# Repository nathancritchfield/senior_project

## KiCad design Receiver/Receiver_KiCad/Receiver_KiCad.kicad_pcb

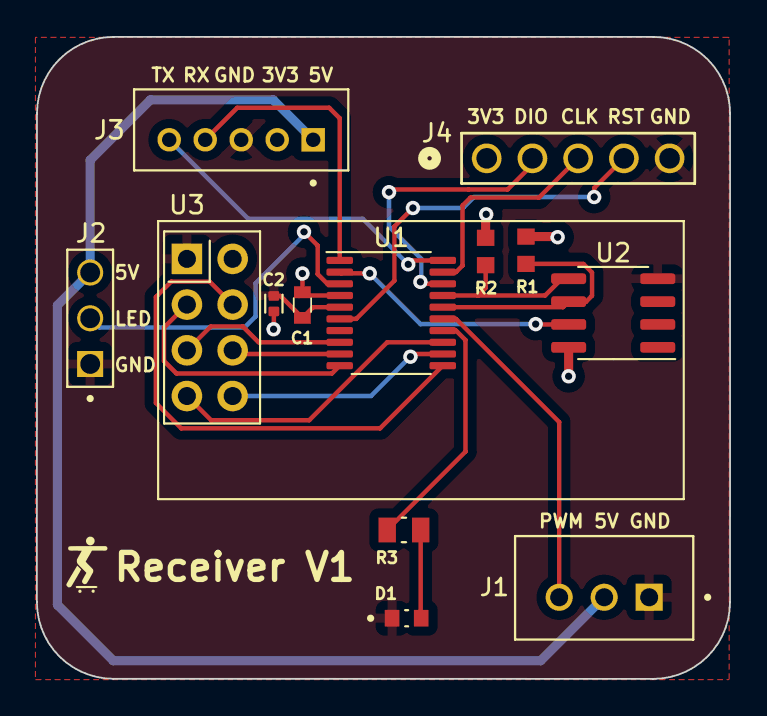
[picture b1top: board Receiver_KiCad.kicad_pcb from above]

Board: 2 copper layers, 38.5 x 35.7 mm, 13 parts (0 on the bottom side), 21 nets.

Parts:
C1: 4u7; CAPC1608X90N
C2: 100n; CAPC1005X55N
D1: LTST-C190GKT; LEDC1608X35N
J1: B3B-XH-A; JST_B3B-XH-A
J2: 61300311121; WURTH_61300311121
J3: B5B-PH-K-S; JST_B5B-PH-K-S
J4: 61300511121; CONN5_0511121_WRE
R1, R2: 4.7k; RESC1508X55N
R3: 120; RESC2012X65N
U1: STM32G031F8Px; TSSOP-20_4.4x6.5mm_P0.65mm
U2: FM24CL16B; SOIC-8_3.9x4.9mm_P1.27mm
U3: NRF24L01_Breakout; nRF24L01_Breakout

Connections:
+5V: J1.2, J2.03, J3.1
/MCU/I2C_SCL: R1.2, U1.16 (PA11/PA9), U2.6 (SCL)
/MCU/I2C_SDA: R2.2, U1.17 (PA12/PA10), U2.5 (SDA)
/MCU/PWM_OUT: J1.3, U1.15 (PB0/PB1/PB2/PA8)
/MCU/SK6812_OUT: J2.02, U1.3 (PC15)
/MCU/SPI1_CE: U1.10 (PA3), U3.3 (CE)
/MCU/SPI1_CSN: U1.11 (PA4), U3.4 (~CSN)
/MCU/SPI1_IRQ: U1.12 (PA5), U3.8 (IRQ)
/MCU/SPI1_MISO: U1.13 (PA6), U3.7 (MISO)
/MCU/SPI1_MOSI: U1.9 (PA2), U3.6 (MOSI)
/MCU/SPI1_SCK: U1.8 (PA1), U3.5 (SCK)
/MCU/STATUS_LED: R3.1, U1.14 (PA7)
/MCU/UART1_RX: J3.4, U1.1 (PB7/PB8)
/MCU/UART1_TX: J3.5, U1.20 (PB3/PB4/PB5/PB6)
/MCU/WP: U1.2 (PC14/PB9), U2.7 (WP)
GND: C1.2, C2.2, D1.C, J1.1, J2.01, J3.3, J4.5, U1.5 (VSS), U2.4 (VSS), U3.1 (GND)
unnamed: D1.A, R3.2
unnamed: J4.2, U1.18 (PA13)
unnamed: J4.3, U1.19 (PA14/PA15)
unnamed: J4.4, U1.6 (PF2)
VDD: C1.1, C2.1, J3.2, J4.1, R1.1, R2.1, U1.4 (VDD), U2.8 (VDD), U3.2 (VCC)

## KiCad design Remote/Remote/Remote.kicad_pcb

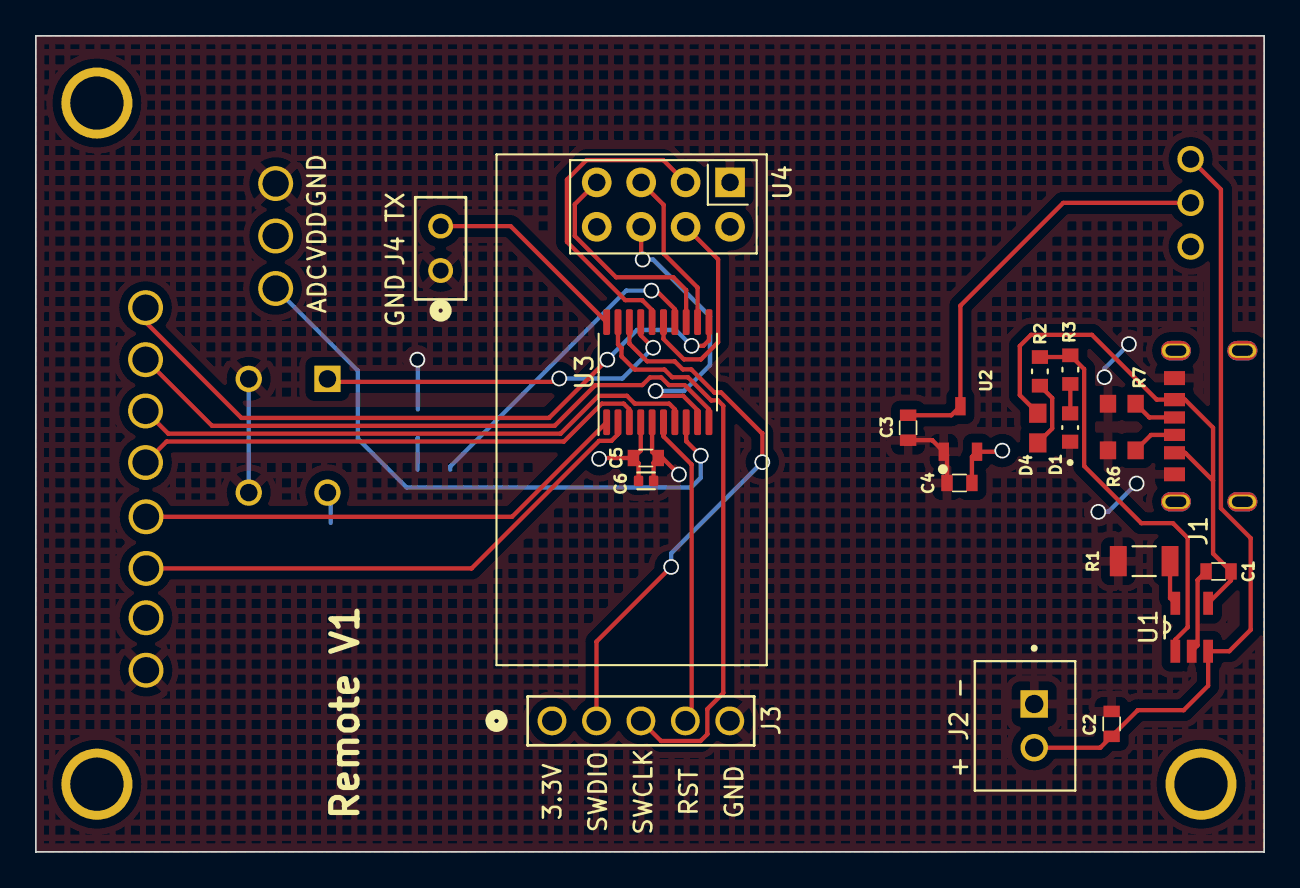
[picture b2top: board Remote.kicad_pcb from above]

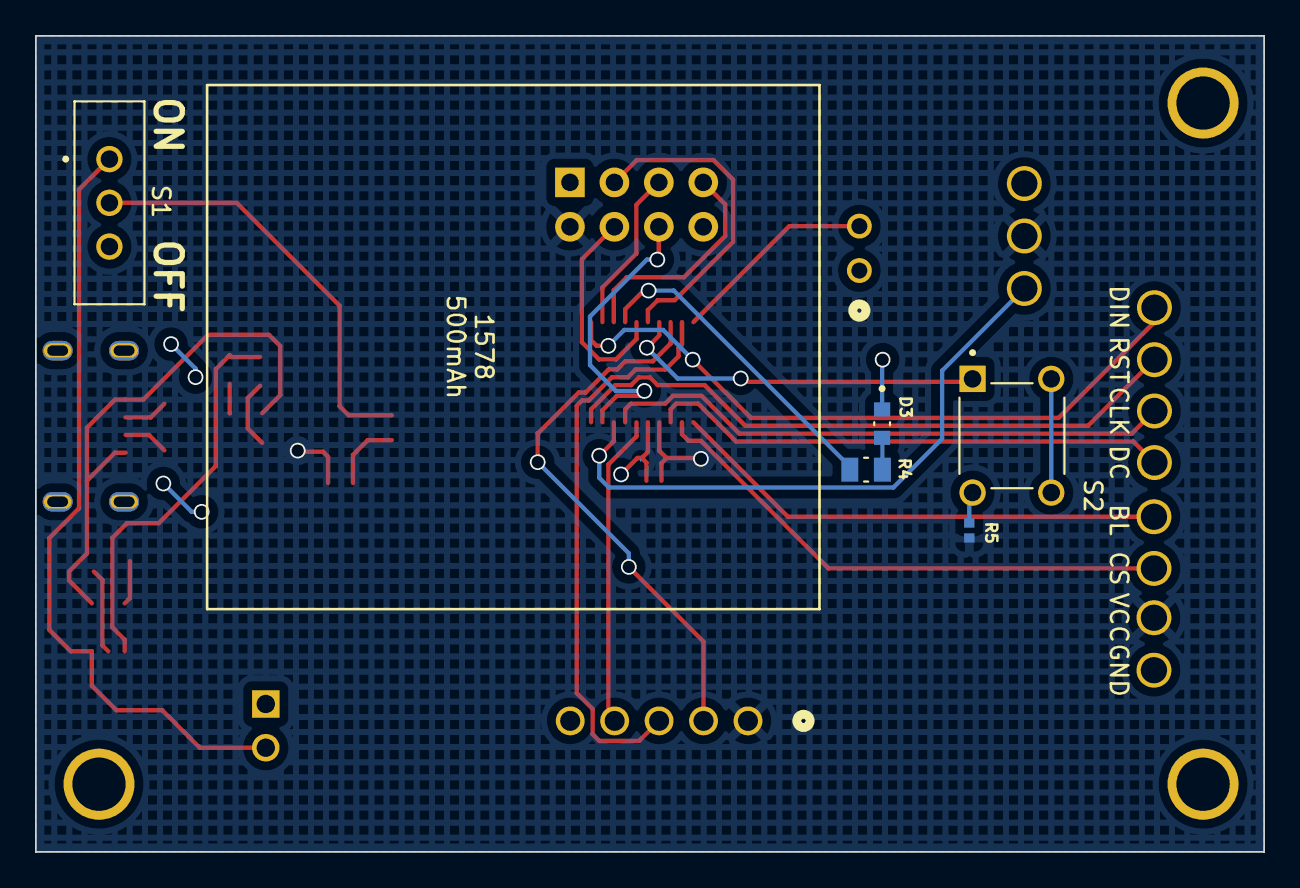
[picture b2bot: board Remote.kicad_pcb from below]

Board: 2 copper layers, 70.2 x 46.7 mm, 37 parts (13 on the bottom side), 31 nets.

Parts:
C1, C2, C3, C4, C5: 4u7; CAPC1608X90N
C6: 100n; CAPC1005X55N
D1: Ready; LEDC1608X35N
D3: LTST-C190GKT; LEDC1608X35N
D4: Charging; 0603
J1: USB4125-GF-A_REVA2; GCT_USB4125-GF-A_REVA2
J2: B2B-XH-A; JST_B2B-XH-A
J3: 61300511121; CONN5_0511121_WRE
J4: M20-9990246; CONN2_M20-999_1x2_HRW
R1: 5k; RESC3116X65N
R2, R3: 250; RESC1608X55N
R4: 120; RESC2012X65N
R5: 4.7k; RESC1005X40N
R6, R7: 5.1k; RESC1608X50N
S1: EG1218; SW_EG1218
S2: TL1105BF160Q; SW_TL1105BF160Q
U1: MCP73831T-2DCI_OT; SOT95P270X145-5N
U2: AP2210N-3.3TRG1; SOT95P280X145-3N
U3: STM32G030F6Px; TSSOP-20_4.4x6.5mm_P0.65mm
U4: NRF24L01_Breakout; nRF24L01_Breakout
U5: ADC; Wire_Via
U6: VDD; Wire_Via
U7, U9: GND; Wire_Via
U8: VCC; Wire_Via
U10: DIN; Wire_Via
U11: CLK; Wire_Via
U12: CS; Wire_Via
U13: DC; Wire_Via
U14: RST; Wire_Via
U15: BL; Wire_Via

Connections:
+5V: C1.1, D4.2, J1.A9 (VBUS), J1.B9 (VBUS__1), U1.4 (VDD)
+BATT: C2.2, J2.2, S1.1, U1.3 (VBAT)
/MCU/ADC1_IN1: U3.8 (PA1), U5.1
/MCU/Button: S2.1, U3.17 (PA12/PA10)
/MCU/Display_BL: U3.1 (PB7/PB8), U15.1
/MCU/Display_DC: U3.3 (PC15), U13.1
/MCU/Display_RST: U3.10 (PA3), U14.1
/MCU/GPIO_Output: R4.1, U3.14 (PA7)
/MCU/SPI1_CE: U3.16 (PA11/PA9), U4.3 (CE)
/MCU/SPI1_CSN: U3.15 (PB0/PB1/PB2/PA8), U4.4 (~CSN)
/MCU/SPI1_MISO: U3.13 (PA6), U4.7 (MISO)
/MCU/SPI1_MOSI: U3.9 (PA2), U4.6 (MOSI)
/MCU/SPI1_SCK: U3.12 (PA5), U4.5 (SCK)
/MCU/SPI2_CS: U3.2 (PC14/PB9), U12.1
/MCU/SPI2_MOSI: U3.11 (PA4), U10.1
/MCU/SPI2_SCK: U3.7 (PA0), U11.1
/MCU/USART1_TX: J4.2, U3.20 (PB3/PB4/PB5/PB6)
GND: C1.2, C2.1, C3.2, C4.1, C5.2, C6.2, D1.C, D3.C, J1.A12 (GND), J1.B12 (GND__1), J2.1, J3.5, J4.1, R1.1, R6.1, R7.1, S2.3, S2.4, U1.2 (VSS), U2.1 (GND), U3.5 (VSS), U4.1 (GND), U7.1, U9.1
unnamed: D1.A, R3.1
unnamed: D3.A, R4.2
unnamed: D4.1, R2.1
unnamed: J1.A5 (CC1), R6.2
unnamed: J1.B5 (CC2), R7.2
unnamed: R5.1, S2.2
unnamed: R1.2, U1.5 (PROG)
unnamed: R2.2, R3.2, U1.1 (STAT)
unnamed: C3.1, S1.2, U2.3 (VIN)
unnamed: J3.4, U3.6 (NRST)
unnamed: J3.2, U3.18 (PA13)
unnamed: J3.3, U3.19 (PA14/PA15)
VDD: C4.2, C5.1, C6.1, J3.1, R5.2, U2.2 (VOUT), U3.4 (VDD), U4.2 (VCC), U6.1, U8.1

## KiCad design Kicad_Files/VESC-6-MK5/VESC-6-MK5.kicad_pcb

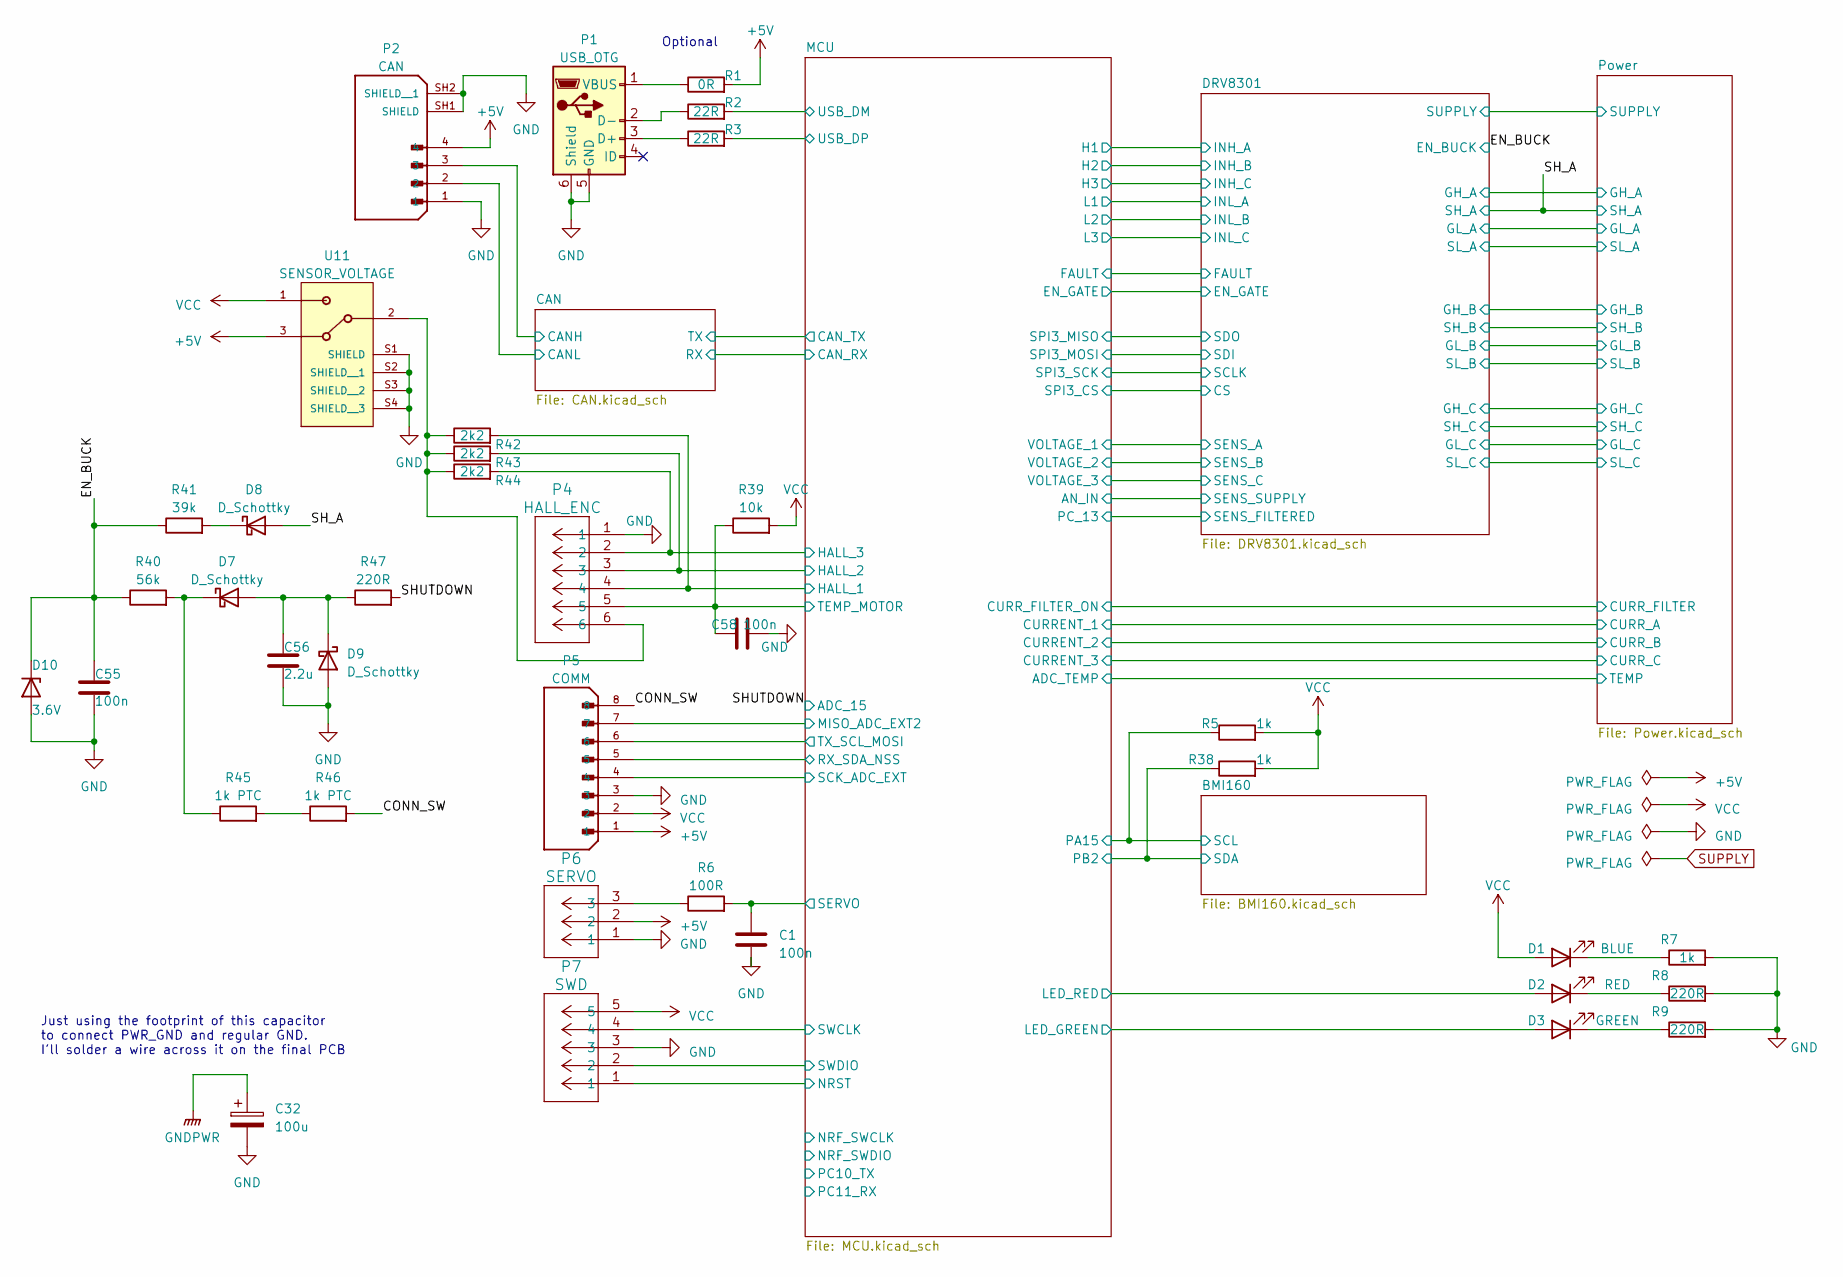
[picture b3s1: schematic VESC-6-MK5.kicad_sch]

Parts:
C1: 100n; CAPC2012X88N
C32: 100u; CAP_TPS1210_3P5X2P8_AVX
C55, C58: 100n; 0603_AVX
C56: 2.2u; CAPC1608X90N
D1: BLUE; LED_LTST-C191KRKT_LTO
D2: RED; LED_LTST-C191KRKT_LTO
D3: GREEN; LED_LTST-C191KGKT_LTO
D7, D8, D9: D_Schottky; CFP3_SOD123W_NEX
D10: 3.6V; SOD-882_TOS
P1: USB_OTG; CONN_S6B-PH-SM4-TBLFSN_JST
P2: CAN; JST_B4B-PH-SM4-TB__LF__SN_; PARTREV N/A
P4: HALL_ENC; CONN_S6B-PH-SM4-TBLFSN_JST
P5: COMM; JST_B8B-PH-SM4-TB_LF__SN_; PARTREV N/A
P6: SERVO; CONN_B3B-PH-SM4-TB_JST
P7: SWD; CONN5_4-TBLFSN_JST
R1: 0R; RESC1608X55N
R2, R3: 22R; RESC3216X70N
R5, R7, R38: 1k; RESC3216X70N
R6: 100R; RES_RK73H2A_KOA
R8, R9, R47: 220R; RESC3216X75N
R39: 10k; RESC1608X55N
R40: 56k; RESC1608X55N
R41: 39k; RESC1608X55N
R42, R43, R44: 2k2; RESC2012X60N
R45, R46: 1k PTC; RESC1608X55N
U11: SENSOR_VOLTAGE; SW_PCM12SMTR; DigiKey_Part_Number 401-2016-2-ND

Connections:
/BMI160/SCL: R5.1; also elsewhere on the board
/BMI160/SDA: R38.1; also elsewhere on the board
/CAN/CANH: P2.3; also elsewhere on the board
/CAN/CANL: P2.2; also elsewhere on the board
/CONN_SW: P5.8, R46.2
/EN_BUCK: C55.1, D10.1 (K), R40.1, R41.1; also elsewhere on the board
/MCU/HALL_1: P4.4, R42.2; also elsewhere on the board
/MCU/HALL_2: P4.3, R43.2; also elsewhere on the board
/MCU/HALL_3: P4.2, R44.2; also elsewhere on the board
/MCU/LED_GREEN: D3.2 (A); also elsewhere on the board
/MCU/LED_RED: D2.2 (A); also elsewhere on the board
/MCU/MISO_ADC_EXT2: P5.7; also elsewhere on the board
/MCU/NRST: P7.1; also elsewhere on the board
/MCU/RX_SDA_NSS: P5.5; also elsewhere on the board
/MCU/SCK_ADC_EXT: P5.4; also elsewhere on the board
/MCU/SERVO: C1.1, R6.2; also elsewhere on the board
/MCU/SWCLK: P7.4; also elsewhere on the board
/MCU/SWDIO: P7.2; also elsewhere on the board
/MCU/TEMP_MOTOR: C58.1, P4.5, R39.1; also elsewhere on the board
/MCU/TX_SCL_MOSI: P5.6; also elsewhere on the board
/MCU/USB_DM: R2.2; also elsewhere on the board
/MCU/USB_DP: R3.2; also elsewhere on the board
/SHUTDOWN: R47.2; also elsewhere on the board
/SH_A: D8.2 (A); also elsewhere on the board
GND: C1.2, C32.2, C55.2, C56.2, C58.2, D9.2 (A), D10.2 (A), P1.5 (GND), P1.6 (Shield), P2.1, P2.SH1 (SHIELD), P2.SH2 (SHIELD__1), P4.1, P5.3, P6.1, P7.3, R7.2, R8.2, R9.2, U11.S1 (SHIELD), U11.S2 (SHIELD__1), U11.S3 (SHIELD__2), U11.S4 (SHIELD__3); also elsewhere on the board
unnamed: D1.1 (K), R7.1
unnamed: D2.1 (K), R8.1
unnamed: D3.1 (K), R9.1
unnamed: C56.1, D7.2 (A), D9.1 (K), R47.1
unnamed: D7.1 (K), R40.2, R45.1
unnamed: D8.1 (K), R41.2
unnamed: P1.3 (D+), R3.1
unnamed: P1.2 (D-), R2.1
unnamed: P1.1 (VBUS), R1.1
unnamed: P4.6, R42.1, R43.1, R44.1, U11.2
unnamed: P6.3, R6.1
unnamed: R45.2, R46.1
VCC: D1.2 (A), P5.2, P7.5, R5.2, R38.2, R39.2, U11.1; also elsewhere on the board

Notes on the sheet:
Just using the footprint of this capacitor to connect PWR_GND and regular GND. I'll solder a wire across it on the final PCB
Optional

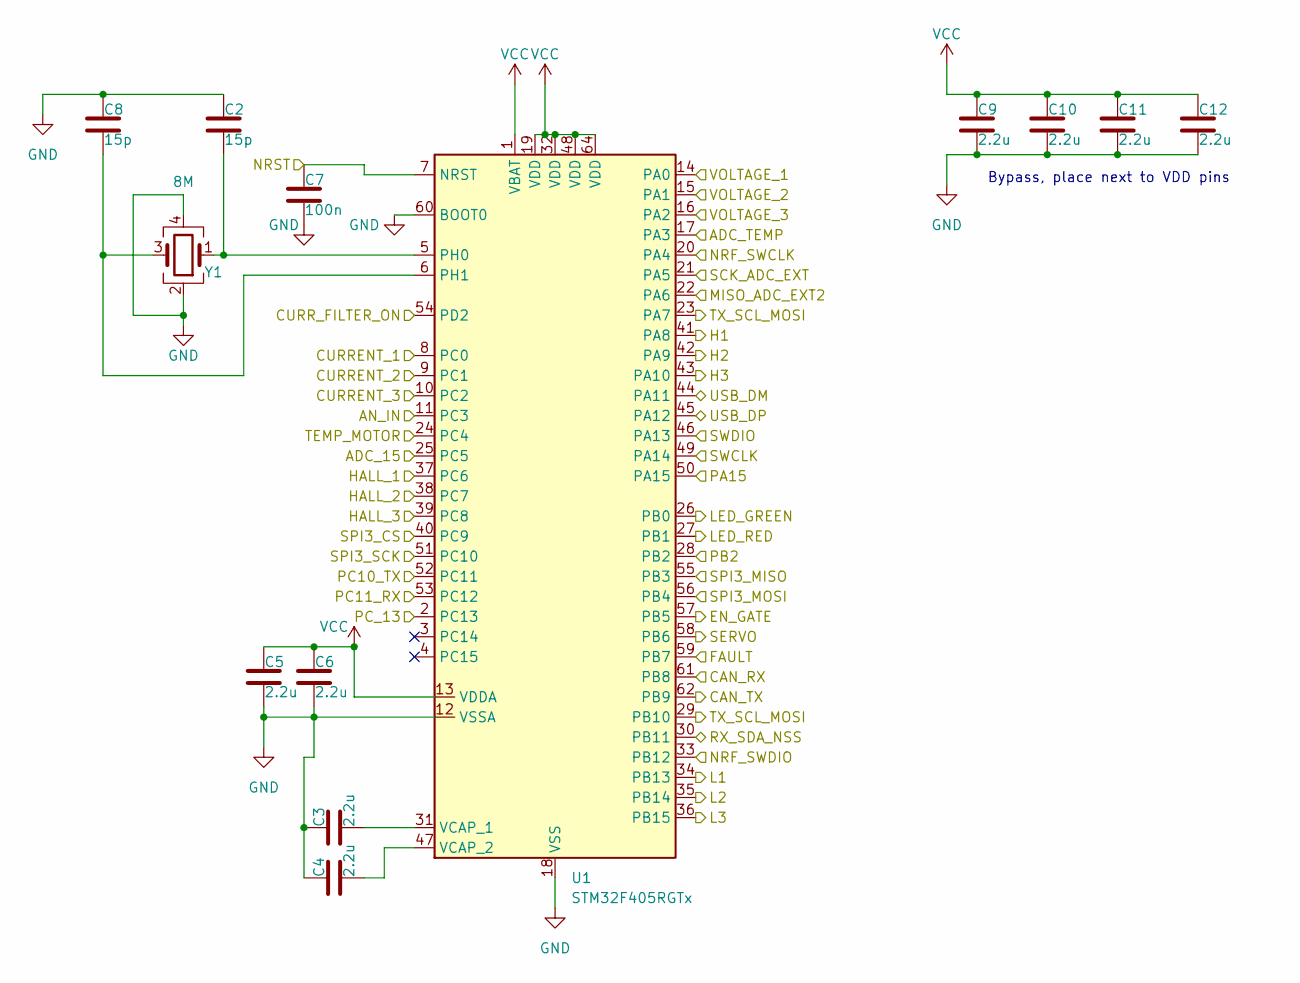
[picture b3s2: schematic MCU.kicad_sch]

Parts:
C2, C8: 15p; CAP_0402C_AVX
C3, C4, C5, C6, C9, C10, C11, C12: 2.2u; CAPC1608X90N
C7: 100n; 0603_AVX
U1: STM32F405RGTx; LQFP-64_10x10mm_P0.5mm
Y1: 8M; XTAL_ABM3B-8.000MHZ-10-1-U-T

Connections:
/BMI160/SCL: U1.50 (PA15); also elsewhere on the board
/BMI160/SDA: U1.28 (PB2); also elsewhere on the board
/CAN/RX: U1.61 (PB8); also elsewhere on the board
/CAN/TX: U1.62 (PB9); also elsewhere on the board
/DRV8301/CS: U1.40 (PC9); also elsewhere on the board
/DRV8301/EN_GATE: U1.57 (PB5); also elsewhere on the board
/DRV8301/FAULT: U1.59 (PB7); also elsewhere on the board
/DRV8301/INH_A: U1.41 (PA8); also elsewhere on the board
/DRV8301/INH_B: U1.42 (PA9); also elsewhere on the board
/DRV8301/INH_C: U1.43 (PA10); also elsewhere on the board
/DRV8301/INL_A: U1.34 (PB13); also elsewhere on the board
/DRV8301/INL_B: U1.35 (PB14); also elsewhere on the board
/DRV8301/INL_C: U1.36 (PB15); also elsewhere on the board
/DRV8301/SCLK: U1.51 (PC10); also elsewhere on the board
/DRV8301/SDI: U1.56 (PB4); also elsewhere on the board
/DRV8301/SDO: U1.55 (PB3); also elsewhere on the board
/DRV8301/SENS_A: U1.14 (PA0); also elsewhere on the board
/DRV8301/SENS_B: U1.15 (PA1); also elsewhere on the board
/DRV8301/SENS_C: U1.16 (PA2); also elsewhere on the board
/DRV8301/SENS_FILTERED: U1.2 (PC13); also elsewhere on the board
/DRV8301/SENS_SUPPLY: U1.11 (PC3); also elsewhere on the board
/MCU/ADC_TEMP: U1.17 (PA3); also elsewhere on the board
/MCU/CURRENT_1: U1.8 (PC0); also elsewhere on the board
/MCU/CURRENT_2: U1.9 (PC1); also elsewhere on the board
/MCU/CURRENT_3: U1.10 (PC2); also elsewhere on the board
/MCU/CURR_FILTER_ON: U1.54 (PD2); also elsewhere on the board
/MCU/HALL_1: U1.37 (PC6); also elsewhere on the board
/MCU/HALL_2: U1.38 (PC7); also elsewhere on the board
/MCU/HALL_3: U1.39 (PC8); also elsewhere on the board
/MCU/LED_GREEN: U1.26 (PB0); also elsewhere on the board
/MCU/LED_RED: U1.27 (PB1); also elsewhere on the board
/MCU/MISO_ADC_EXT2: U1.22 (PA6); also elsewhere on the board
/MCU/NRF_SWCLK: U1.20 (PA4)
/MCU/NRF_SWDIO: U1.33 (PB12)
/MCU/NRST: C7.1, U1.7 (NRST); also elsewhere on the board
/MCU/PC10_TX: U1.52 (PC11)
/MCU/PC11_RX: U1.53 (PC12)
/MCU/RX_SDA_NSS: U1.30 (PB11); also elsewhere on the board
/MCU/SCK_ADC_EXT: U1.21 (PA5); also elsewhere on the board
/MCU/SERVO: U1.58 (PB6); also elsewhere on the board
/MCU/SWCLK: U1.49 (PA14); also elsewhere on the board
/MCU/SWDIO: U1.46 (PA13); also elsewhere on the board
/MCU/TEMP_MOTOR: U1.24 (PC4); also elsewhere on the board
/MCU/TX_SCL_MOSI: U1.23 (PA7), U1.29 (PB10); also elsewhere on the board
/MCU/USB_DM: U1.44 (PA11); also elsewhere on the board
/MCU/USB_DP: U1.45 (PA12); also elsewhere on the board
/SHUTDOWN: U1.25 (PC5); also elsewhere on the board
GND: C2.1, C3.1, C4.1, C5.2, C6.2, C7.2, C8.1, C9.2, C10.2, C11.2, C12.2, U1.12 (VSSA), U1.18 (VSS), U1.60 (BOOT0), U1.63 (VSS), Y1.2, Y1.4; also elsewhere on the board
unnamed: C2.2, U1.5 (PH0), Y1.1
unnamed: C8.2, U1.6 (PH1), Y1.3
unnamed: C3.2, U1.31 (VCAP_1)
unnamed: C4.2, U1.47 (VCAP_2)
VCC: C5.1, C6.1, C9.1, C10.1, C11.1, C12.1, U1.1 (VBAT), U1.13 (VDDA), U1.19 (VDD), U1.32 (VDD), U1.48 (VDD), U1.64 (VDD); also elsewhere on the board

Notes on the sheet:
Bypass, place next to VDD pins

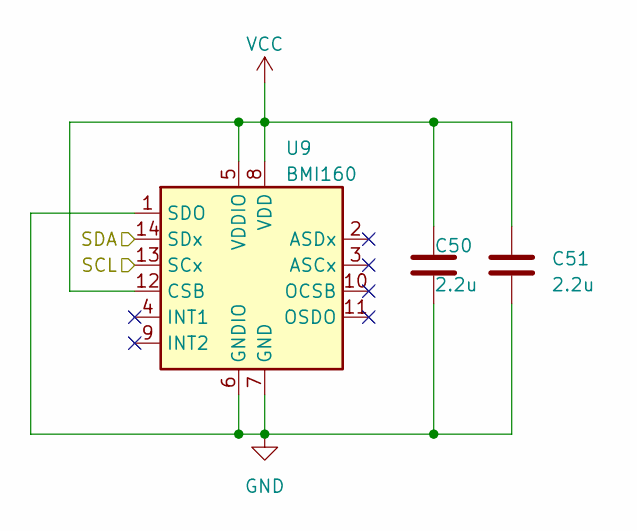
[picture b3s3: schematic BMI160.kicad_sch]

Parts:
C50, C51: 2.2u; CAPC1608X90N
U9: BMI160; Bosch_LGA-14_3x2.5mm_P0.5mm

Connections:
/BMI160/SCL: U9.13 (SCx); also elsewhere on the board
/BMI160/SDA: U9.14 (SDx); also elsewhere on the board
GND: C50.2, C51.2, U9.1 (SDO), U9.6 (GNDIO), U9.7 (GND); also elsewhere on the board
VCC: C50.1, C51.1, U9.5 (VDDIO), U9.8 (VDD), U9.12 (CSB); also elsewhere on the board

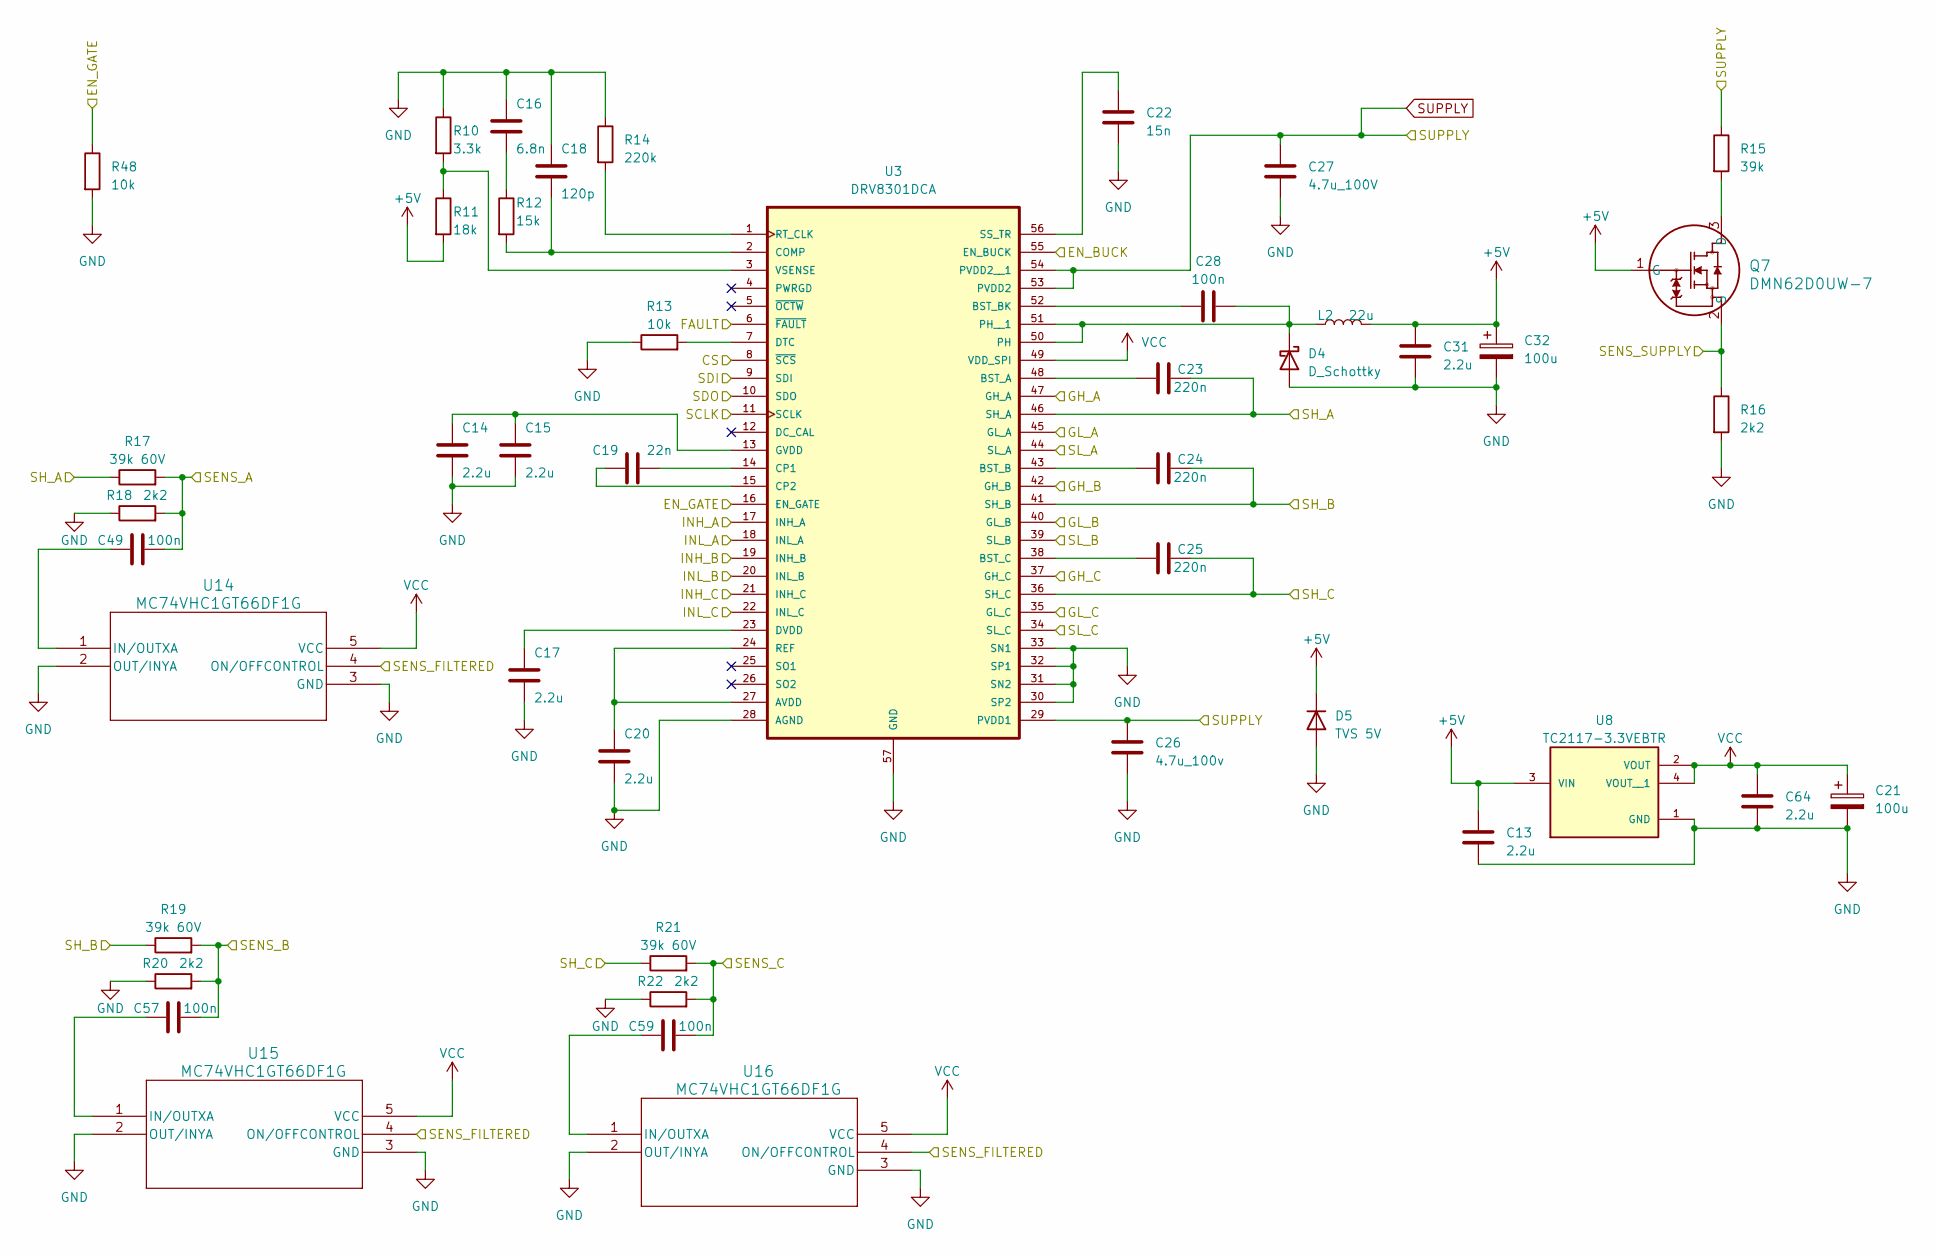
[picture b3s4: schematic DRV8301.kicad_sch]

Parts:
C13, C14, C15, C17, C20, C31, C64: 2.2u; CAPC1608X90N
C16: 6.8n; CAP_C0805C-GEC-DG_KEM
C18: 120p; CAP_0603G_AVX
C19: 22n; CAPC10555_55N_KEM
C21, C32: 100u; CAP_TPS1210_3P5X2P8_AVX
C22: 15n; CAPC340180_88N_KEM
C23, C24, C25: 220n; CAPC1608X90N
C26: 4.7u_100v; CAPC3216X190N
C27: 4.7u_100V; CAPC3216X190N
C28, C49, C57, C59: 100n; 0603_AVX
D4: D_Schottky; CFP3_SOD123W_NEX
D5: TVS 5V; DIOM4325X250N
L2: 22u; IND_BOURNS_SDR0805
Q7: DMN62D0UW-7; SOT323_DMN62D0UV_DIO
R10: 3.3k; RESC1608X55N
R11: 18k; RESC1608X55N
R12: 15k; RESC1608X55N
R13, R48: 10k; RESC1608X55N
R14: 220k; RESC1608X55N
R15: 39k; RESC1608X55N
R16, R18, R20, R22: 2k2; RESC1608X55N
R17, R19, R21: 39k 60V; RESC6332X70N
U3: DRV8301DCA; SOP50P810X120-57N; PARTREV F
U8: TC2117-3.3VEBTR; TO254P1491X483-4N
U14, U15, U16: MC74VHC1GT66DF1G; SC-88A_ONS

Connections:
/DRV8301/CS: U3.8 (~SCS); also elsewhere on the board
/DRV8301/EN_GATE: R48.1, U3.16 (EN_GATE); also elsewhere on the board
/DRV8301/FAULT: U3.6 (~FAULT); also elsewhere on the board
/DRV8301/GH_A: U3.47 (GH_A); also elsewhere on the board
/DRV8301/GH_B: U3.42 (GH_B); also elsewhere on the board
/DRV8301/GH_C: U3.37 (GH_C); also elsewhere on the board
/DRV8301/GL_A: U3.45 (GL_A); also elsewhere on the board
/DRV8301/GL_B: U3.40 (GL_B); also elsewhere on the board
/DRV8301/GL_C: U3.35 (GL_C); also elsewhere on the board
/DRV8301/INH_A: U3.17 (INH_A); also elsewhere on the board
/DRV8301/INH_B: U3.19 (INH_B); also elsewhere on the board
/DRV8301/INH_C: U3.21 (INH_C); also elsewhere on the board
/DRV8301/INL_A: U3.18 (INL_A); also elsewhere on the board
/DRV8301/INL_B: U3.20 (INL_B); also elsewhere on the board
/DRV8301/INL_C: U3.22 (INL_C); also elsewhere on the board
/DRV8301/SCLK: U3.11 (SCLK); also elsewhere on the board
/DRV8301/SDI: U3.9 (SDI); also elsewhere on the board
/DRV8301/SDO: U3.10 (SDO); also elsewhere on the board
/DRV8301/SENS_A: C49.2, R17.2, R18.2; also elsewhere on the board
/DRV8301/SENS_B: C57.2, R19.2, R20.2; also elsewhere on the board
/DRV8301/SENS_C: C59.2, R21.2, R22.2; also elsewhere on the board
/DRV8301/SENS_FILTERED: U14.4 (ON/OFFCONTROL), U15.4 (ON/OFFCONTROL), U16.4 (ON/OFFCONTROL); also elsewhere on the board
/DRV8301/SENS_SUPPLY: Q7.2 (S), R16.1; also elsewhere on the board
/DRV8301/SH_B: C24.2, R19.1, U3.41 (SH_B); also elsewhere on the board
/DRV8301/SH_C: C25.2, R21.1, U3.36 (SH_C); also elsewhere on the board
/EN_BUCK: U3.55 (EN_BUCK); also elsewhere on the board
/SH_A: C23.2, R17.1, U3.46 (SH_A); also elsewhere on the board
GND: C13.2, C14.2, C15.2, C16.1, C17.2, C18.1, C20.2, C21.2, C22.2, C26.2, C27.2, C31.2, C32.2, C64.2, D4.2 (A), D5.2 (A), R10.1, R13.1, R14.1, R16.2, R18.1, R20.1, R22.1, R48.2, U3.28 (AGND), U3.30 (SP2), U3.31 (SN2), U3.32 (SP1), U3.33 (SN1), U3.34 (SL_C), U3.39 (SL_B), U3.44 (SL_A), U3.57 (GND), U8.1 (GND), U14.2 (OUT/INYA), U14.3 (GND), U15.2 (OUT/INYA), U15.3 (GND), U16.2 (OUT/INYA), U16.3 (GND); also elsewhere on the board
unnamed: C16.2, R12.1
unnamed: C28.2, D4.1 (K), L2.1, U3.50 (PH), U3.51 (PH__1)
unnamed: Q7.3 (D), R15.2
unnamed: C20.1, U3.24 (REF), U3.27 (AVDD)
unnamed: C23.1, U3.48 (BST_A)
unnamed: C24.1, U3.43 (BST_B)
unnamed: C28.1, U3.52 (BST_BK)
unnamed: C25.1, U3.38 (BST_C)
unnamed: C18.2, R12.2, U3.2 (COMP)
unnamed: C19.2, U3.14 (CP1)
unnamed: C19.1, U3.15 (CP2)
unnamed: R13.2, U3.7 (DTC)
unnamed: C17.1, U3.23 (DVDD)
unnamed: C14.1, C15.1, U3.13 (GVDD)
unnamed: R14.2, U3.1 (RT_CLK)
unnamed: C22.1, U3.56 (SS_TR)
unnamed: R10.2, R11.1, U3.3 (VSENSE)
unnamed: C49.1, U14.1 (IN/OUTXA)
unnamed: C57.1, U15.1 (IN/OUTXA)
unnamed: C59.1, U16.1 (IN/OUTXA)
SUPPLY: C26.1, C27.1, R15.1, U3.29 (PVDD1), U3.53 (PVDD2), U3.54 (PVDD2__1); also elsewhere on the board
VCC: C21.1, C64.1, U3.49 (VDD_SPI), U8.2 (VOUT), U8.4 (VOUT__1), U14.5 (VCC), U15.5 (VCC), U16.5 (VCC); also elsewhere on the board

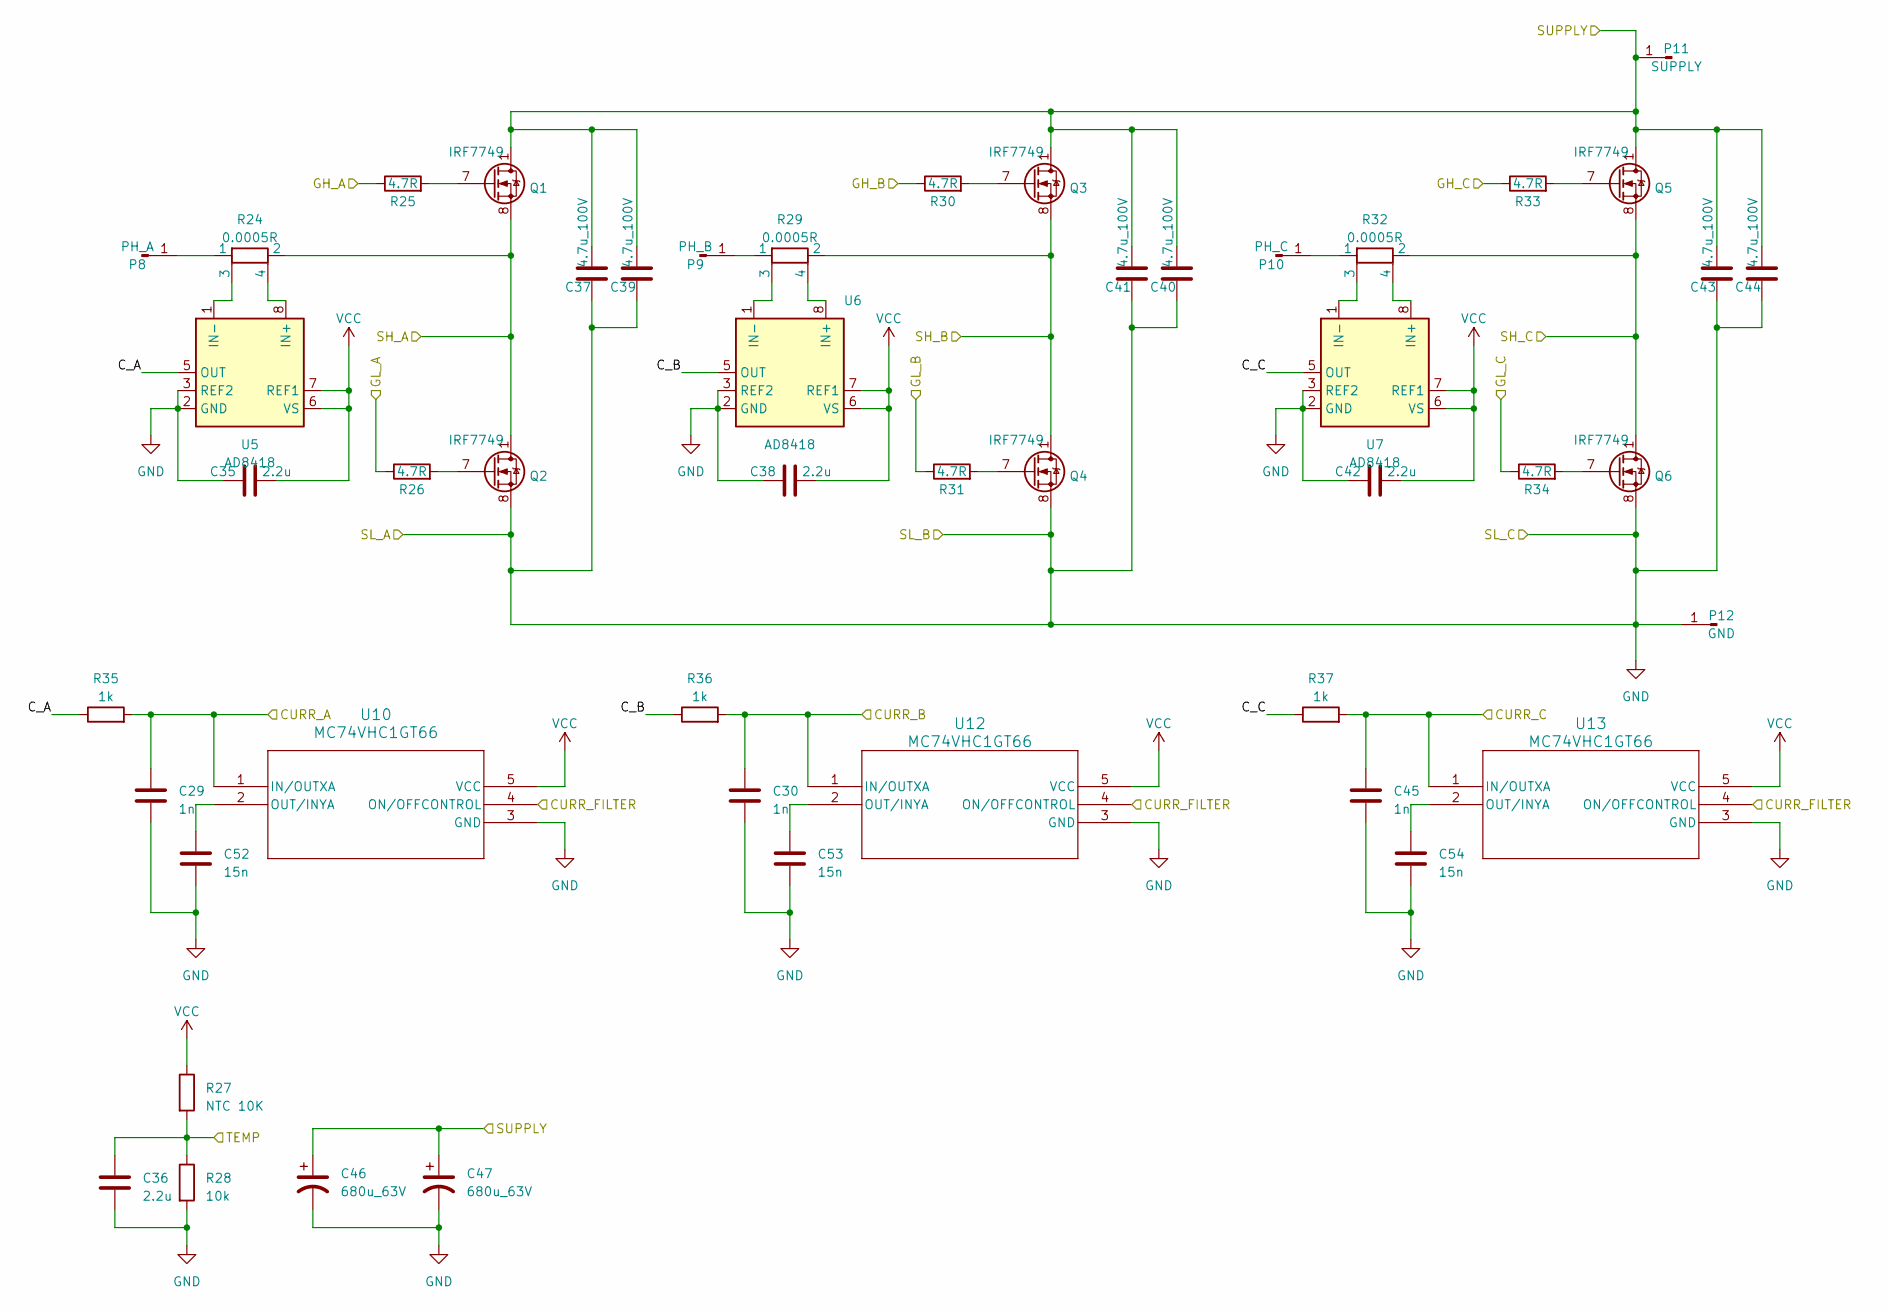
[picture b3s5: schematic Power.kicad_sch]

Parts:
C29, C30, C45: 1n; CAPC2012X88N
C35, C36, C38, C42: 2.2u; CAPC1608X90N
C37, C39, C40, C41, C43, C44: 4.7u_100V; CAPC3216X190N
C46, C47: 680u_63V; CAPPRD500W80D1250H3500
C52, C53, C54: 15n; CAPC340180_88N_KEM
P8: PH_A; 8x8mm Solder Pad
P9: PH_B; 8x8mm Solder Pad
P10: PH_C; 8x8mm Solder Pad
P11: SUPPLY; 8x8mm Solder Pad
P12: GND; 8x8mm Solder Pad
Q1, Q2, Q3, Q4, Q5, Q6: IRF7749; DIRECTFET_L8_INF
R24, R29, R32: 0.0005R; RES_WSLP2726L5000FEA
R25, R26, R30, R31, R33, R34: 4.7R; RESC1608X55N
R27: NTC 10K; THERM_ERT-JZEG103FA
R28: 10k; RESC1608X55N
R35, R36, R37: 1k; RESC3216X70N
U5, U6, U7: AD8418; SOP65P490X110-8N
U10, U12, U13: MC74VHC1GT66; SC-88A_ONS

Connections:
/DRV8301/GH_A: R25.1; also elsewhere on the board
/DRV8301/GH_B: R30.1; also elsewhere on the board
/DRV8301/GH_C: R33.1; also elsewhere on the board
/DRV8301/GL_A: R26.1; also elsewhere on the board
/DRV8301/GL_B: R31.1; also elsewhere on the board
/DRV8301/GL_C: R34.1; also elsewhere on the board
/DRV8301/SH_B: Q3.8 (S), Q4.1 (D), R29.2; also elsewhere on the board
/DRV8301/SH_C: Q5.8 (S), Q6.1 (D), R32.2; also elsewhere on the board
/MCU/ADC_TEMP: C36.1, R27.2, R28.1; also elsewhere on the board
/MCU/CURRENT_1: C29.1, R35.2, U10.1 (IN/OUTXA); also elsewhere on the board
/MCU/CURRENT_2: C30.1, R36.2, U12.1 (IN/OUTXA); also elsewhere on the board
/MCU/CURRENT_3: C45.1, R37.2, U13.1 (IN/OUTXA); also elsewhere on the board
/MCU/CURR_FILTER_ON: U10.4 (ON/OFFCONTROL), U12.4 (ON/OFFCONTROL), U13.4 (ON/OFFCONTROL); also elsewhere on the board
/Power/C_A: R35.1, U5.5 (OUT)
/Power/C_B: R36.1, U6.5 (OUT)
/Power/C_C: R37.1, U7.5 (OUT)
/SH_A: Q1.8 (S), Q2.1 (D), R24.2; also elsewhere on the board
GND: C29.2, C30.2, C35.1, C36.2, C37.1, C38.1, C39.1, C40.1, C41.1, C42.1, C43.1, C44.1, C45.2, C46.2, C47.2, C52.2, C53.2, C54.2, P12.1, Q2.8 (S), Q4.8 (S), Q6.8 (S), R28.2, U5.2 (GND), U5.3 (REF2), U6.2 (GND), U6.3 (REF2), U7.2 (GND), U7.3 (REF2), U10.3 (GND), U12.3 (GND), U13.3 (GND); also elsewhere on the board
unnamed: P8.1, R24.1
unnamed: P9.1, R29.1
unnamed: P10.1, R32.1
unnamed: Q1.7 (G), R25.2
unnamed: Q2.7 (G), R26.2
unnamed: Q3.7 (G), R30.2
unnamed: Q4.7 (G), R31.2
unnamed: Q5.7 (G), R33.2
unnamed: Q6.7 (G), R34.2
unnamed: R24.4, U5.8 (IN+)
unnamed: R24.3, U5.1 (IN-)
unnamed: R29.4, U6.8 (IN+)
unnamed: R29.3, U6.1 (IN-)
unnamed: R32.4, U7.8 (IN+)
unnamed: R32.3, U7.1 (IN-)
unnamed: C52.1, U10.2 (OUT/INYA)
unnamed: C53.1, U12.2 (OUT/INYA)
unnamed: C54.1, U13.2 (OUT/INYA)
SUPPLY: C37.2, C39.2, C40.2, C41.2, C43.2, C44.2, C46.1, C47.1, P11.1, Q1.1 (D), Q3.1 (D), Q5.1 (D); also elsewhere on the board
VCC: C35.2, C38.2, C42.2, R27.1, U5.6 (VS), U5.7 (REF1), U6.6 (VS), U6.7 (REF1), U7.6 (VS), U7.7 (REF1), U10.5 (VCC), U12.5 (VCC), U13.5 (VCC); also elsewhere on the board

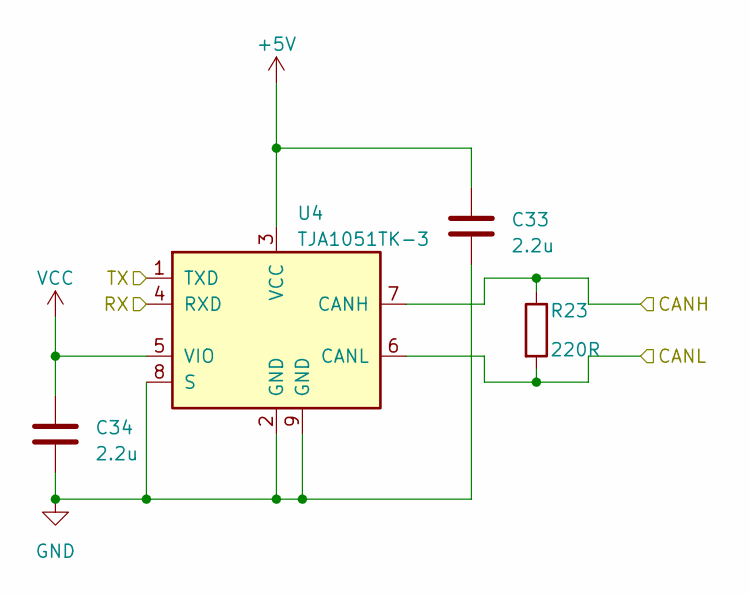
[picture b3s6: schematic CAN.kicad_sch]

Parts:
C33, C34: 2.2u; CAPC1608X90N
R23: 220R; RESC3216X75N
U4: TJA1051TK-3; DFN-8-1EP_3x3mm_P0.65mm_EP1.55x2.4mm

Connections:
/CAN/CANH: R23.1, U4.7 (CANH); also elsewhere on the board
/CAN/CANL: R23.2, U4.6 (CANL); also elsewhere on the board
/CAN/RX: U4.4 (RXD); also elsewhere on the board
/CAN/TX: U4.1 (TXD); also elsewhere on the board
GND: C33.2, C34.2, U4.2 (GND), U4.8 (S), U4.9 (GND); also elsewhere on the board
VCC: C34.1, U4.5 (VIO); also elsewhere on the board

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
